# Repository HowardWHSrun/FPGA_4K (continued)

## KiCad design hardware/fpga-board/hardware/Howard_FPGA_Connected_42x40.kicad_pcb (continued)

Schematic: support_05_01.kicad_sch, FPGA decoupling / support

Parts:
C1: 680uF; CP_EIA-7343-43_Kemet-X__C1; Tolerance TBD; Voltage rating TBD; MPN TBD
C2: 4.7uF; C_0402_1005Metric__C2; Tolerance 10%; Voltage rating 10 V; MPN C1005X5R1A475K050BC
C3: 4.7uF; C_0402_1005Metric__C3; Tolerance 10%; Voltage rating 10 V; MPN C1005X5R1A475K050BC
C4: 4.7uF; C_0402_1005Metric__C4; Tolerance 10%; Voltage rating 10 V; MPN C1005X5R1A475K050BC
C5: 4.7uF; C_0402_1005Metric__C5; Tolerance 10%; Voltage rating 10 V; MPN C1005X5R1A475K050BC
C6: 4.7uF; C_0402_1005Metric__C6; Tolerance 10%; Voltage rating 10 V; MPN C1005X5R1A475K050BC
C7: 4.7uF; C_0402_1005Metric__C7; Tolerance 10%; Voltage rating 10 V; MPN C1005X5R1A475K050BC
C8: 4.7uF; C_0402_1005Metric__C8; Tolerance 10%; Voltage rating 10 V; MPN C1005X5R1A475K050BC
C9: 4.7uF; C_0402_1005Metric__C9; Tolerance 10%; Voltage rating 10 V; MPN C1005X5R1A475K050BC
C10: 4.7uF; C_0402_1005Metric__C10; Tolerance 10%; Voltage rating 10 V; MPN C1005X5R1A475K050BC
C11: 4.7uF; C_0402_1005Metric__C11; Tolerance 10%; Voltage rating 10 V; MPN C1005X5R1A475K050BC
C12: 4.7uF; C_0402_1005Metric__C12; Tolerance 10%; Voltage rating 10 V; MPN C1005X5R1A475K050BC
C13: 4.7uF; C_0402_1005Metric__C13; Tolerance 10%; Voltage rating 10 V; MPN C1005X5R1A475K050BC
C14: 0.47uF; C_0201_0603Metric__C14; Tolerance 20%; Voltage rating 10 V; MPN C0603X5R1A474M030BC
C15: 0.47uF; C_0201_0603Metric__C15; Tolerance 20%; Voltage rating 10 V; MPN C0603X5R1A474M030BC
C16: 0.47uF; C_0201_0603Metric__C16; Tolerance 20%; Voltage rating 10 V; MPN C0603X5R1A474M030BC

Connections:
+1V0: C1.1, C2.1, C3.1, C4.1, C5.1, C6.1, C7.1, C8.1, C9.1, C10.1, C11.1, C12.1, C13.1, C14.1, C15.1, C16.1; also elsewhere on the board
GND: C1.2, C2.2, C3.2, C4.2, C5.2, C6.2, C7.2, C8.2, C9.2, C10.2, C11.2, C12.2, C13.2, C14.2, C15.2, C16.2; also elsewhere on the board

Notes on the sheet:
GLOBAL LABELS ARE ELECTRICAL CONNECTIONS. TBD values are unresolved parts. DNP positions are optional or isolation provisions; open pins
FPGA decoupling / support
remain visible to ERC.

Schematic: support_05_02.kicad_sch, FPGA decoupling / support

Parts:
C17: 0.47uF; C_0201_0603Metric__C17; Tolerance 20%; Voltage rating 10 V; MPN C0603X5R1A474M030BC
C18: 0.47uF; C_0201_0603Metric__C18; Tolerance 20%; Voltage rating 10 V; MPN C0603X5R1A474M030BC
C19: 0.47uF; C_0201_0603Metric__C19; Tolerance 20%; Voltage rating 10 V; MPN C0603X5R1A474M030BC
C20: 0.47uF; C_0201_0603Metric__C20; Tolerance 20%; Voltage rating 10 V; MPN C0603X5R1A474M030BC
C21: 0.47uF; C_0201_0603Metric__C21; Tolerance 20%; Voltage rating 10 V; MPN C0603X5R1A474M030BC
C22: 0.47uF; C_0201_0603Metric__C22; Tolerance 20%; Voltage rating 10 V; MPN C0603X5R1A474M030BC
C23: 0.47uF; C_0201_0603Metric__C23; Tolerance 20%; Voltage rating 10 V; MPN C0603X5R1A474M030BC
C24: 0.47uF; C_0201_0603Metric__C24; Tolerance 20%; Voltage rating 10 V; MPN C0603X5R1A474M030BC
C25: 0.47uF; C_0201_0603Metric__C25; Tolerance 20%; Voltage rating 10 V; MPN C0603X5R1A474M030BC
C26: 0.47uF; C_0201_0603Metric__C26; Tolerance 20%; Voltage rating 10 V; MPN C0603X5R1A474M030BC
C27: 0.47uF; C_0201_0603Metric__C27; Tolerance 20%; Voltage rating 10 V; MPN C0603X5R1A474M030BC
C28: 100uF; C_1210_3225Metric__C28; Tolerance TBD; Voltage rating TBD; MPN TBD
C29: 0.47uF; C_0201_0603Metric__C29; Tolerance 20%; Voltage rating 10 V; MPN C0603X5R1A474M030BC
C30: 0.47uF; C_0201_0603Metric__C30; Tolerance 20%; Voltage rating 10 V; MPN C0603X5R1A474M030BC
C31: 0.47uF; C_0201_0603Metric__C31; Tolerance 20%; Voltage rating 10 V; MPN C0603X5R1A474M030BC
C32: 47uF; C_1210_3225Metric__C32; Tolerance TBD; Voltage rating TBD; MPN TBD

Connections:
+1V0: C17.1, C18.1, C19.1, C20.1, C21.1, C22.1, C23.1, C24.1, C25.1, C26.1, C27.1, C28.1, C29.1, C30.1, C31.1; also elsewhere on the board
+1V8: C32.1; also elsewhere on the board
GND: C17.2, C18.2, C19.2, C20.2, C21.2, C22.2, C23.2, C24.2, C25.2, C26.2, C27.2, C28.2, C29.2, C30.2, C31.2, C32.2; also elsewhere on the board

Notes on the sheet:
GLOBAL LABELS ARE ELECTRICAL CONNECTIONS. TBD values are unresolved parts. DNP positions are optional or isolation provisions; open pins
FPGA decoupling / support
remain visible to ERC.

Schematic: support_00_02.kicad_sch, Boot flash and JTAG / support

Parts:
C101: 100nF; C_0402_1005Metric__C101; Tolerance 10%; Voltage rating 16 V; MPN C1005X7R1C104K050BC
C102: 1uF; C_0402_1005Metric__C102; Tolerance 10%; Voltage rating 35 V; MPN C1005X5R1V105K050BC
R115: 0Ohm; R_0201_0603Metric__R115; Tolerance jumper <=50mOhm; Voltage rating 30 V limiting voltage; MPN CRCW02010000Z0ED

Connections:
+3V3: C101.1, C102.1; also elsewhere on the board
GND: C101.2, C102.2; also elsewhere on the board
QSPI_IO3: R115.2; also elsewhere on the board
QSPI_IO3_FPGA: R115.1; also elsewhere on the board

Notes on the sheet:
GLOBAL LABELS ARE ELECTRICAL CONNECTIONS. TBD values are unresolved parts. DNP positions are optional or isolation provisions; open pins
Boot flash and JTAG / support
remain visible to ERC.

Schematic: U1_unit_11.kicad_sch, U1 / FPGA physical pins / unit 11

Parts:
U1: XC7A200T-1SBG484C; Xilinx_SBG484__U1; Tolerance TBD; Voltage rating TBD; MPN XC7A200T-1SBG484C

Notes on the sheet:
U1 / FPGA physical pins / unit 11
bank plan or timing constraints.
Exact XC7A200T SBG484 physical pin map. Boot and core rails are drafted. Unassigned acquisition/link/DDR pins remain open; no completed

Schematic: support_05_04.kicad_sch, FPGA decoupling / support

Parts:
C49: 4.7uF; C_0402_1005Metric__C49; Tolerance 10%; Voltage rating 10 V; MPN C1005X5R1A475K050BC
C50: 4.7uF; C_0402_1005Metric__C50; Tolerance 10%; Voltage rating 10 V; MPN C1005X5R1A475K050BC
C51: 0.47uF; C_0201_0603Metric__C51; Tolerance 20%; Voltage rating 10 V; MPN C0603X5R1A474M030BC
C52: 0.47uF; C_0201_0603Metric__C52; Tolerance 20%; Voltage rating 10 V; MPN C0603X5R1A474M030BC
C53: 0.47uF; C_0201_0603Metric__C53; Tolerance 20%; Voltage rating 10 V; MPN C0603X5R1A474M030BC
C54: 0.47uF; C_0201_0603Metric__C54; Tolerance 20%; Voltage rating 10 V; MPN C0603X5R1A474M030BC
C55: 47uF; C_1210_3225Metric__C55; Tolerance TBD; Voltage rating TBD; MPN TBD
C56: 4.7uF; C_0402_1005Metric__C56; Tolerance 10%; Voltage rating 10 V; MPN C1005X5R1A475K050BC
C57: 4.7uF; C_0402_1005Metric__C57; Tolerance 10%; Voltage rating 10 V; MPN C1005X5R1A475K050BC
C58: 0.47uF; C_0201_0603Metric__C58; Tolerance 20%; Voltage rating 10 V; MPN C0603X5R1A474M030BC
C59: 0.47uF; C_0201_0603Metric__C59; Tolerance 20%; Voltage rating 10 V; MPN C0603X5R1A474M030BC
C60: 0.47uF; C_0201_0603Metric__C60; Tolerance 20%; Voltage rating 10 V; MPN C0603X5R1A474M030BC
C61: 0.47uF; C_0201_0603Metric__C61; Tolerance 20%; Voltage rating 10 V; MPN C0603X5R1A474M030BC
C62: 47uF; C_1210_3225Metric__C62; Tolerance TBD; Voltage rating TBD; MPN TBD
C63: 4.7uF; C_0402_1005Metric__C63; Tolerance 10%; Voltage rating 10 V; MPN C1005X5R1A475K050BC
C64: 4.7uF; C_0402_1005Metric__C64; Tolerance 10%; Voltage rating 10 V; MPN C1005X5R1A475K050BC

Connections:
+3V3: C49.1, C50.1, C51.1, C52.1, C53.1, C54.1, C55.1; also elsewhere on the board
GND: C49.2, C50.2, C51.2, C52.2, C53.2, C54.2, C55.2, C56.2, C57.2, C58.2, C59.2, C60.2, C61.2, C62.2, C63.2, C64.2; also elsewhere on the board
VCCO_15_TBD: C56.1, C57.1, C58.1, C59.1, C60.1, C61.1, C62.1; also elsewhere on the board
VCCO_16_TBD: C63.1, C64.1; also elsewhere on the board

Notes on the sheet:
GLOBAL LABELS ARE ELECTRICAL CONNECTIONS. TBD values are unresolved parts. DNP positions are optional or isolation provisions; open pins
FPGA decoupling / support
remain visible to ERC.

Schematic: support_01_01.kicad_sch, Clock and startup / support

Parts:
C120: TBD oscillator bypass; C_0603_1608Metric__C120; Tolerance TBD; Voltage rating TBD; MPN TBD
R120: TBD clock series resistor; R_0402_1005Metric__R120; Tolerance TBD; Voltage rating TBD; MPN TBD
R121: TBD oscillator control resistor; R_0402_1005Metric__R121; Tolerance TBD; Voltage rating TBD; MPN TBD
Y1: Oscillator frequency / MPN TBD; Oscillator_SMD_Abracon_ASE-4Pin_3.2x2.5mm__Y1; Tolerance TBD; Voltage rating TBD; MPN TBD

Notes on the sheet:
GLOBAL LABELS ARE ELECTRICAL CONNECTIONS. TBD values are unresolved parts. DNP positions are optional or isolation provisions; open pins
remain visible to ERC.
Clock and startup / support

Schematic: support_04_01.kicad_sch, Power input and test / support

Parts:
F1: FUSE / rating TBD; Fuse_1206_3216Metric__F1; Tolerance TBD; Voltage rating TBD; MPN TBD
J5: DC INPUT / 12V proposal; JST_PH_B2B-PH-K_1x02_P2.00mm_Vertical__J5; Tolerance TBD; Voltage rating TBD; MPN TBD
TP1: GND; TestPoint_Pad_D1.0mm__TP1; Tolerance TBD; Voltage rating TBD; MPN PCB copper test pad
TP2: VIN_PROTECTED; TestPoint_Pad_D1.0mm__TP2; Tolerance TBD; Voltage rating TBD; MPN PCB copper test pad
TP3: +1V0; TestPoint_Pad_D1.0mm__TP3; Tolerance TBD; Voltage rating TBD; MPN PCB copper test pad
TP4: +1V8; TestPoint_Pad_D1.0mm__TP4; Tolerance TBD; Voltage rating TBD; MPN PCB copper test pad
TP5: +1V5; TestPoint_Pad_D1.0mm__TP5; Tolerance TBD; Voltage rating TBD; MPN PCB copper test pad
TP6: +3V3; TestPoint_Pad_D1.0mm__TP6; Tolerance TBD; Voltage rating TBD; MPN PCB copper test pad
TP7: PROGRAM_B; TestPoint_Pad_D1.0mm__TP7; Tolerance TBD; Voltage rating TBD; MPN PCB copper test pad
TP8: DONE; TestPoint_Pad_D1.0mm__TP8; Tolerance TBD; Voltage rating TBD; MPN PCB copper test pad

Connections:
+1V0: TP3.1; also elsewhere on the board
+1V5: TP5.1; also elsewhere on the board
+1V8: TP4.1; also elsewhere on the board
+3V3: TP6.1; also elsewhere on the board
DONE: TP8.1; also elsewhere on the board
GND: J5.2, TP1.1; also elsewhere on the board
PROGRAM_B: TP7.1; also elsewhere on the board
VIN_PROTECTED: F1.2, TP2.1; also elsewhere on the board
VIN_RAW: F1.1, J5.1

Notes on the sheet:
GLOBAL LABELS ARE ELECTRICAL CONNECTIONS. TBD values are unresolved parts. DNP positions are optional or isolation provisions; open pins
Power input and test / support
remain visible to ERC.

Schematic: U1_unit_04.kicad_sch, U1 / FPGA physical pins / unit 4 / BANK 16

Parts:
U1: XC7A200T-1SBG484C; Xilinx_SBG484__U1; Tolerance TBD; Voltage rating TBD; MPN XC7A200T-1SBG484C

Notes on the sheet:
U1 / FPGA physical pins / unit 4 / BANK 16
bank plan or timing constraints.
Exact XC7A200T SBG484 physical pin map. Boot and core rails are drafted. Unassigned acquisition/link/DDR pins remain open; no completed

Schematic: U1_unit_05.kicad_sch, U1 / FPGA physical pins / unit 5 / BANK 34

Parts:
U1: XC7A200T-1SBG484C; Xilinx_SBG484__U1; Tolerance TBD; Voltage rating TBD; MPN XC7A200T-1SBG484C

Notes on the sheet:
bank plan or timing constraints.
Exact XC7A200T SBG484 physical pin map. Boot and core rails are drafted. Unassigned acquisition/link/DDR pins remain open; no completed
U1 / FPGA physical pins / unit 5 / BANK 34

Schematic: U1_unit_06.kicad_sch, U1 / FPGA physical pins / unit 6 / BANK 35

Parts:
U1: XC7A200T-1SBG484C; Xilinx_SBG484__U1; Tolerance TBD; Voltage rating TBD; MPN XC7A200T-1SBG484C

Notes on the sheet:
bank plan or timing constraints.
U1 / FPGA physical pins / unit 6 / BANK 35
Exact XC7A200T SBG484 physical pin map. Boot and core rails are drafted. Unassigned acquisition/link/DDR pins remain open; no completed

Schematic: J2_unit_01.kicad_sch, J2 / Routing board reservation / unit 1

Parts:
J2: Routing 80-contact / proxy; Hirose_DF40C-80DS-0.4V_2x40_P0.4mm__J2; Tolerance TBD; Voltage rating TBD; MPN TBD

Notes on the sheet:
and Gerald.
J2 / Routing board reservation / unit 1
Routing-to-FPGA connector SPACE RESERVATION B. Coordinate carrier revision, grounds, clock/control sharing and power handoff with Zitong

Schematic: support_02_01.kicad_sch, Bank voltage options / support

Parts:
R130: 0R / DNP; R_0402_1005Metric__R130; Tolerance TBD; Voltage rating TBD; MPN TBD; not fitted
R131: 0R / DNP; R_0402_1005Metric__R131; Tolerance TBD; Voltage rating TBD; MPN TBD; not fitted
R132: 0R / DNP; R_0402_1005Metric__R132; Tolerance TBD; Voltage rating TBD; MPN TBD; not fitted
R133: 0R / DNP; R_0402_1005Metric__R133; Tolerance TBD; Voltage rating TBD; MPN TBD; not fitted
R134: 0R / DNP; R_0402_1005Metric__R134; Tolerance TBD; Voltage rating TBD; MPN TBD; not fitted

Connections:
+1V5: R131.1, R132.1, R133.1, R134.1; also elsewhere on the board
+3V3: R130.1; also elsewhere on the board
VCCO_13_TBD: R130.2; also elsewhere on the board
VCCO_15_TBD: R131.2; also elsewhere on the board
VCCO_16_TBD: R132.2; also elsewhere on the board
VCCO_34_TBD: R133.2; also elsewhere on the board
VCCO_35_TBD: R134.2; also elsewhere on the board

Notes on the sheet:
GLOBAL LABELS ARE ELECTRICAL CONNECTIONS. TBD values are unresolved parts. DNP positions are optional or isolation provisions; open pins
Bank voltage options / support
remain visible to ERC.

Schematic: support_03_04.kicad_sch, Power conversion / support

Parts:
C319: 100uF 6.3V local-output PROVISIONAL; C_1210_3225Metric__C319; Tolerance TBD; Voltage rating TBD; MPN TBD
C320: 100uF 6.3V local-output PROVISIONAL; C_1210_3225Metric__C320; Tolerance TBD; Voltage rating TBD; MPN TBD
C321: 47uF 6.3V local-output PROVISIONAL; C_1210_3225Metric__C321; Tolerance TBD; Voltage rating TBD; MPN TBD
C322: 47uF 6.3V local-output PROVISIONAL; C_1210_3225Metric__C322; Tolerance TBD; Voltage rating TBD; MPN TBD
C323: 47uF 6.3V local-output PROVISIONAL; C_1210_3225Metric__C323; Tolerance TBD; Voltage rating TBD; MPN TBD
C324: 22uF 6.3V local-output PROVISIONAL; C_1210_3225Metric__C324; Tolerance TBD; Voltage rating TBD; MPN TBD
C325: 22uF 6.3V local-output PROVISIONAL; C_1210_3225Metric__C325; Tolerance TBD; Voltage rating TBD; MPN TBD
C326: 22uF 6.3V local-output PROVISIONAL; C_1210_3225Metric__C326; Tolerance TBD; Voltage rating TBD; MPN TBD
C327: 22uF 6.3V local-output PROVISIONAL; C_1210_3225Metric__C327; Tolerance TBD; Voltage rating TBD; MPN TBD

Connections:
+1V0: C319.1, C320.1; also elsewhere on the board
+1V5: C324.1, C325.1; also elsewhere on the board
+1V8: C321.1, C322.1, C323.1; also elsewhere on the board
+3V3: C326.1, C327.1; also elsewhere on the board
GND: C319.2, C320.2, C321.2, C322.2, C323.2, C324.2, C325.2, C326.2, C327.2; also elsewhere on the board

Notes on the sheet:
GLOBAL LABELS ARE ELECTRICAL CONNECTIONS. TBD values are unresolved parts. DNP positions are optional or isolation provisions; open pins
Power conversion / support
remain visible to ERC.

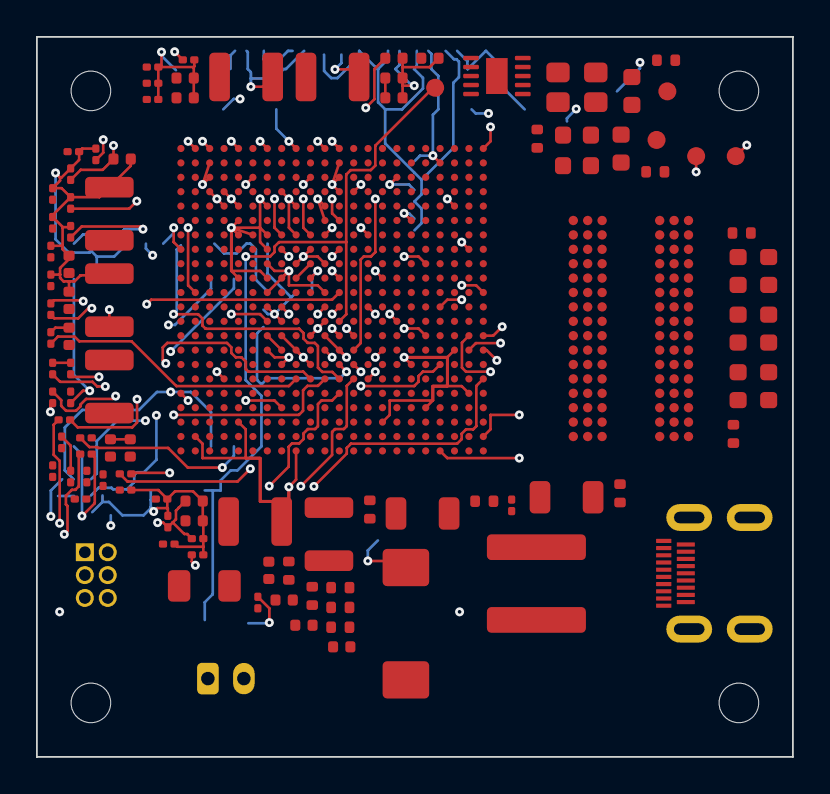
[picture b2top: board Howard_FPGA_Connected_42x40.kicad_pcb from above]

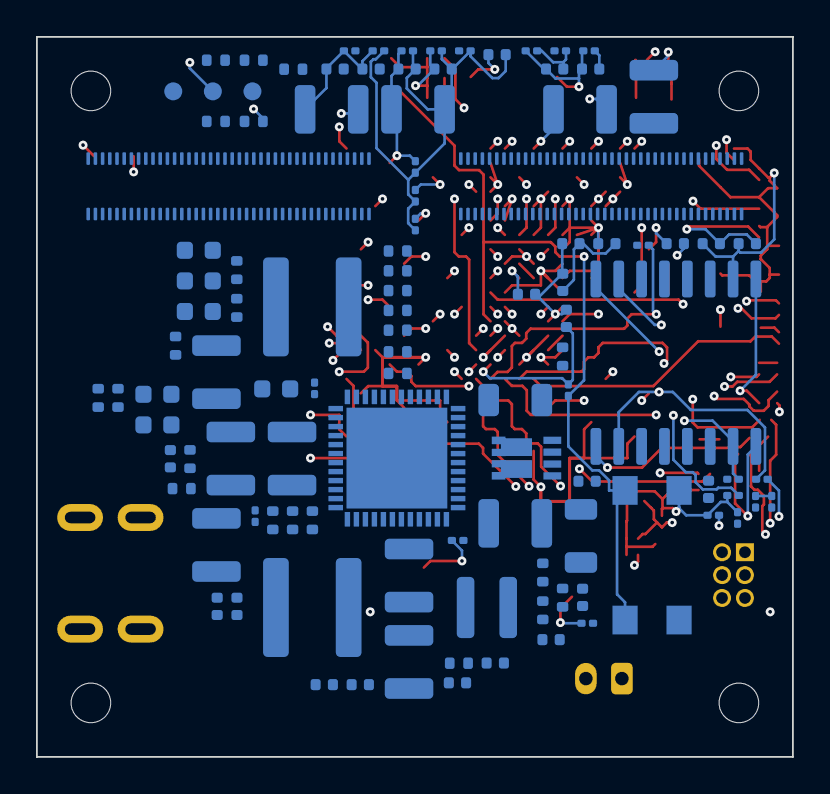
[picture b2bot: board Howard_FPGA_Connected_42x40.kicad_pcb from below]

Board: 8 copper layers, 42.0 x 40.0 mm, 214 parts (108 on the bottom side), 65 nets.

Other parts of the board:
J3: Micro-HDMI / custom-link pinout TBD; HDMI_Micro-D_Molex_46765-1xxx__J3

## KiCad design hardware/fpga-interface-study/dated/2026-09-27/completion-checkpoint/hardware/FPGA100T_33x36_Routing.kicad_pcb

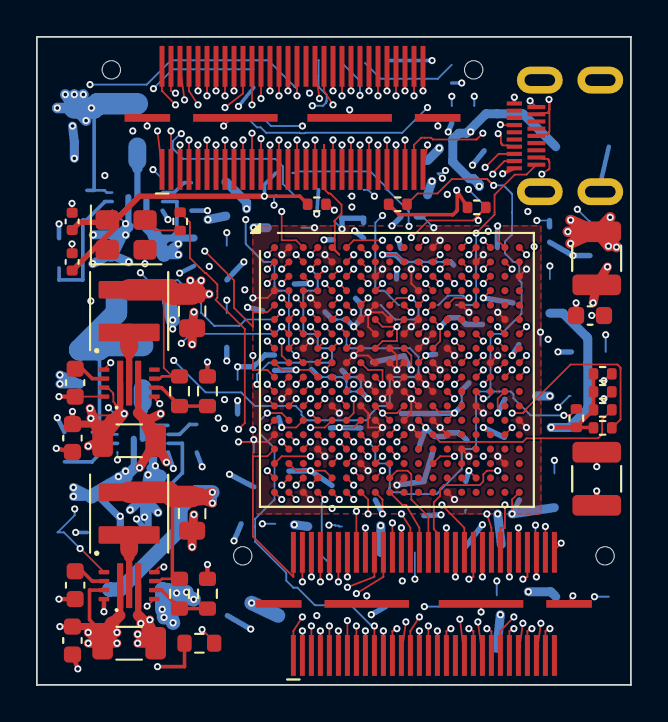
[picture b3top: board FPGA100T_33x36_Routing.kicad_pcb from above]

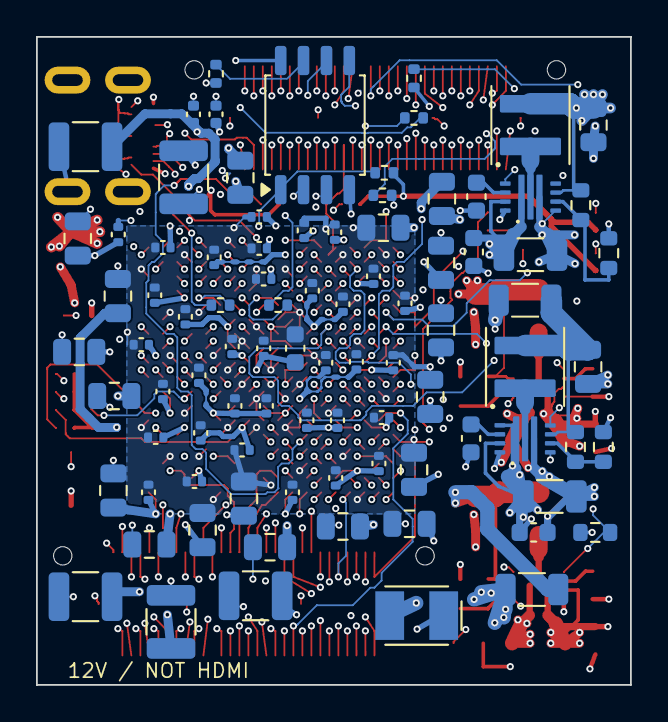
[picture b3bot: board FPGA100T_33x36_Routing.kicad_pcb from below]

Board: 12 copper layers, 33.0 x 36.0 mm, 125 parts (89 on the bottom side), 159 nets.

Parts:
C1: 47u 25V X5R; Capacitor_SMD__C_1210_3225Metric
C2, C4, C8, C12, C16: 100n 100V X7R; Capacitor_SMD__C_0603_1608Metric
C3, C7, C11, C15: 22u 25V X5R; Capacitor_SMD__C_1206_3216Metric
C5, C9, C13, C17: 22u 16V X5R; Capacitor_SMD__C_0805_2012Metric
C6, C10, C14, C18: 10n 50V X7R; Capacitor_SMD__C_0603_1608Metric
C20: 330u 2.5V POSCAP ESR9m@300kHz; Panasonic_POSCAP_B2_Recommended
C21: 100u 6.3V X5R; Capacitor_SMD__C_1210_3225Metric
C22, C23, C24, C25, C26, C27, C41, C42, C51, C52, C57, C58, C64, C65, C70, C71, C76, C77: 4.7u 10V X7R; Capacitor_SMD__C_0805_2012Metric
C28, C29, C30, C31, C32, C33, C34, C35, C36, C37, C43, C44, C45, C46, C53, C54, C55, C56, C59, C60, C61, C62, C66, C67, C68, C69, C72, C73, C74, C75, C78, C79, C80, C81: 470n 10V X7R; Murata_GRT15_0402_Recommended
C40, C50, C63, C82, C92: 47u 6.3V X7R; Capacitor_SMD__C_1210_3225Metric
C90: 100n 16V X7R; Murata_GRT15_0402_Recommended
C91: 1u 10V X7R; Capacitor_SMD__C_0603_1608Metric
C100, C103: 100n; Capacitor_SMD__C_0402_1005Metric
C101: 1u 16V X5R; Capacitor_SMD__C_0402_1005Metric
C102: 10n; Capacitor_SMD__C_0402_1005Metric
J4: CUSTOM POWER + JTAG / DATA TBD; LinkPort__MicroHDMI_46765_1xxx
J5, J6: QSH-030-01-L-D-A; Samtec_QSH-030-01-L-D-A
L1, L2, L3, L4: 1uH 5.4A Isat30%; PowerDraft__L_Coilcraft_XFL4020
R1: 32.4k 0.1%; Resistor_SMD__R_0603_1608Metric
R2, R4, R6, R8: 69.8k 0.1%; Resistor_SMD__R_0603_1608Metric
R3: 110k 0.1%; Resistor_SMD__R_0603_1608Metric
R5: 180k 0.1%; Resistor_SMD__R_0603_1608Metric
R7: 80.6k 0.1%; Resistor_SMD__R_0603_1608Metric
R9: 12m 1% 1W; Resistor_SMD__R_1206_3216Metric
R10, R11: 100k; Resistor_SMD__R_0603_1608Metric
R100: 2.4k; Resistor_SMD__R_0402_1005Metric
R101, R102, R108, R109, R110: 4.7k; Resistor_SMD__R_0402_1005Metric
R103, R105, R118, R119: 33; Resistor_SMD__R_0402_1005Metric
R104: 0; Resistor_SMD__R_0402_1005Metric
R111, R114: 1k; Resistor_SMD__R_0402_1005Metric
R115, R116, R117: 10k; Resistor_SMD__R_0402_1005Metric
R122: 15m 1% 1W; Resistor_SMD__R_1206_3216Metric
U1: XC7A100T-1CSG324I; Xilinx_CSG324
U2, U3, U4, U5: TPS62135RGXR; PowerDraft__Texas_VQFN_RGX0011A_2x3mm
U6: MX25U12835FM2I-10G; Package_SO__SOIC-8_5_3x5_3mm_P1_27mm
Y1: ASE3 32MHz 1.8V; Oscillator__Oscillator_SMD_Abracon_ASE-4Pin_3_2x2_5mm

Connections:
ASIC1_CLK32MHz_Out: J5.9, U1.E2
ASIC1_DATA1: J5.1, U1.K1
ASIC1_DATA2: J5.2, U1.F1
ASIC1_DATA3: J5.3, U1.K2
ASIC1_DATA4: J5.4, U1.E1
ASIC1_DATA5: J5.5, U1.H1
ASIC1_DATA6: J5.6, U1.G2
ASIC1_DATA7: J5.7, U1.G1
ASIC1_DATA8: J5.8, U1.C1
ASIC1_READ: J5.10, U1.B1
ASIC1_SYNC: J5.11, U1.J2
ASIC2_CLK32MHz_Out: J5.20, U1.E3
ASIC2_DATA1: J5.12, U1.C2
ASIC2_DATA2: J5.13, U1.H2
ASIC2_DATA3: J5.14, U1.B3
ASIC2_DATA4: J5.15, U1.J3
ASIC2_DATA5: J5.16, U1.A3
ASIC2_DATA6: J5.17, U1.G3
ASIC2_DATA7: J5.18, U1.C4
ASIC2_DATA8: J5.19, U1.A1
ASIC2_READ: J5.21, U1.B2
ASIC2_SYNC: J5.22, U1.B4
ASIC3_CLK32MHz_Out: J5.31, U1.F4
ASIC3_DATA1: J5.23, U1.J4
ASIC3_DATA2: J5.24, U1.J5
ASIC3_DATA3: J5.25, U1.H4
ASIC3_DATA4: J5.26, U1.F5
ASIC3_DATA5: J5.27, U1.G4
ASIC3_DATA6: J5.28, U1.E5
ASIC3_DATA7: J5.29, U1.H5
ASIC3_DATA8: J5.30, U1.G6
ASIC3_READ: J5.32, U1.E6
ASIC3_SYNC: J5.33, U1.H6
ASIC4_CLK32MHz_Out: J5.42, U1.D5
ASIC4_DATA1: J6.60, U1.C5
ASIC4_DATA2: J5.35, U1.A4
ASIC4_DATA3: J5.36, U1.C6
ASIC4_DATA4: J5.37, U1.A5
ASIC4_DATA5: J5.38, U1.A6
ASIC4_DATA6: J5.39, U1.B6
ASIC4_DATA7: J5.40, U1.C7
ASIC4_DATA8: J5.41, U1.E7
ASIC4_READ: J5.43, U1.B7
ASIC4_SYNC: J5.44, U1.D8
ASIC5_CLK32MHz_Out: J6.9, U1.R3
ASIC5_DATA1: J6.1, U1.V1
ASIC5_DATA2: J6.2, U1.R1
ASIC5_DATA3: J6.3, U1.U1
ASIC5_DATA4: J6.4, U1.U2
ASIC5_DATA5: J6.5, U1.T1
ASIC5_DATA6: J6.6, U1.R2
ASIC5_DATA7: J6.7, U1.V2
ASIC5_DATA8: J6.8, U1.U3
ASIC5_READ: J6.10, U1.V4
ASIC5_SYNC: J6.11, U1.P2
ASIC6_CLK32MHz_Out: J6.20, U1.P4
ASIC6_DATA1: J6.12, U1.M2
ASIC6_DATA2: J6.13, U1.N1
ASIC6_DATA3: J6.14, U1.M3
ASIC6_DATA4: J6.15, U1.M1
ASIC6_DATA5: J6.16, U1.K3
ASIC6_DATA6: J6.17, U1.L1
ASIC6_DATA7: J6.18, U1.N4
ASIC6_DATA8: J6.19, U1.N2
ASIC6_READ: J6.21, U1.L3
ASIC6_SYNC: J6.22, U1.R6
ASIC7_CLK32MHz_Out: J6.31, U1.T5
ASIC7_DATA1: J6.23, U1.U4
ASIC7_DATA2: J6.24, U1.V7
ASIC7_DATA3: J6.25, U1.V5
ASIC7_DATA4: J6.26, U1.U7
ASIC7_DATA5: J6.27, U1.V6
ASIC7_DATA6: J6.28, U1.U8
ASIC7_DATA7: J6.29, U1.U6
ASIC7_DATA8: J6.30, U1.V9
ASIC7_READ: J6.32, U1.U9
ASIC7_SYNC: J6.33, U1.T6
ASIC8_CLK32MHz_Out: J6.42, U1.N5
ASIC8_DATA1: J6.34, U1.M6
ASIC8_DATA2: J6.35, U1.M4
ASIC8_DATA3: J6.36, U1.R8
ASIC8_DATA4: J6.58, U1.L4
ASIC8_DATA5: J6.38, U1.K5
ASIC8_DATA6: J6.39, U1.R7
ASIC8_DATA7: J6.40, U1.L6
ASIC8_DATA8: J6.41, U1.N6
ASIC8_READ: J6.43, U1.T8
ASIC8_SYNC: J6.44, U1.K6
BOARD1_CLK: J5.54, U1.B16
BOARD1_SPI_CLK: J5.58, U1.B17
BOARD2_CLK: J5.55, U1.B13
BOARD2_SPI_CLK: J5.59, U1.A14
BOARD3_CLK: J5.56, U1.A16
BOARD3_SPI_CLK: J5.60, U1.A18
BOARD4_CLK: J5.57, U1.C14
BOARD4_SPI_CLK: J6.45, U1.K13
CFG_M0: R111.2, U1.P12
CFG_PUDC_B: R114.2, U1.L15
CHIP_RESET_SHARED: J5.45, U1.D12
CLK_32MHZ: R119.2, U1.P17
FB_ASIC: R7.2, R8.1, U5.5
FB_AUX: R3.2, R4.1, U3.5
FB_CFG: R5.2, R6.1, U4.5
FB_CORE: R1.2, R2.1, U2.5
FE_RESET_SHARED: J5.48, U1.B14
FLASH_CS_B: R100.2, U1.L13, U6.1
FLASH_DQ0: R104.2, U6.5
FLASH_DQ1: R105.2, U6.2
FLASH_DQ2: R101.2, U6.3
FLASH_DQ3: R102.2, U6.7
FLASH_SCLK: R103.2, U6.6
FPGA_CCLK: R103.1, U1.E9
FPGA_CFG_DQ0: R104.1, U1.K17
FPGA_CFG_DQ1: R105.1, U1.K18
FPGA_DONE: R110.2, U1.P10
FPGA_INIT_B: R109.2, U1.P7
FPGA_PROGRAM_B: R108.2, U1.P9
FPGA_TDO: R118.1, U1.E13
GND: C1.2, C2.2, C3.2, C4.2, C5.2, C6.2, C7.2, C8.2, C9.2, C10.2, C11.2, C12.2, C13.2, C14.2, C15.2, C16.2, C17.2, C18.2, C20.2, C21.2, C22.2, C23.2, C24.2, C25.2, C26.2, C27.2, C28.2, C29.2, C30.2, C31.2, C32.2, C33.2, C34.2, C35.2, C36.2, C37.2, C40.2, C41.2, C42.2, C43.2, C44.2, C45.2, C46.2, C50.2, C51.2, C52.2, C53.2, C54.2, C55.2, C56.2, C57.2, C58.2, C59.2, C60.2, C61.2, C62.2, C63.2, C64.2, C65.2, C66.2, C67.2, C68.2, C69.2, C70.2, C71.2, C72.2, C73.2, C74.2, C75.2, C76.2, C77.2, C78.2, C79.2, C80.2, C81.2, C82.2, C90.2, C91.2, C92.2, C100.2, C101.2, C102.2, C103.2, J4.4, J4.7, J4.10, J4.13, J4.16, J4.SH, J5.G, J6.G, R2.2, R4.2, R6.2, R8.2, U1.A2, U1.A12, U1.B5, U1.B15, U1.C8, U1.C18, U1.D1, U1.D11, U1.E4, U1.E8, U1.E14, U1.F7, U1.F9, U1.F11, U1.F17, U1.G8, U1.G10, U1.G12, U1.H3, U1.H7, U1.H9, U1.H11, U1.H13, U1.J6, U1.J8, U1.J9, U1.J10, U1.J12, U1.J16, U1.K7, U1.K9, U1.K10, U1.K11, U1.L2, U1.L8, U1.L9, U1.L10, U1.L12, U1.M5, U1.M7, U1.M9, U1.M11, U1.M15, U1.N8, U1.N10, U1.N12, U1.N18, U1.P1, U1.P8, U1.P11, U1.P13, U1.R4, U1.R14, U1.T7, U1.T17, U1.U10, U1.V3, U1.V13, U2.3, U2.4, U2.11, U3.3, U3.4, U3.11, U4.3, U4.4, U4.11, U5.3, U5.4, U5.11, U6.4, Y1.2
IMP_TST_SHARED: J5.47, U1.B11
JTAG_TCK: J4.17, R117.2, U1.E10
JTAG_TDI: J4.15, R116.2, U1.E11
JTAG_TDO: J4.18, R118.2
JTAG_TMS: J4.2, R115.2, U1.E12
LINK_12V: C1.1, C2.1, C3.1, C4.1, C7.1, C8.1, C11.1, C12.1, C15.1, C16.1, J4.19, R10.1, R11.1, U2.1, U2.8, U2.10, U3.1, U3.10, U4.1, U4.10, U5.1, U5.10
NONSTIM_BOARD1_SPI_DL: J6.54, U1.G17
NONSTIM_BOARD1_SPI_DR: J6.55, U1.H17
NONSTIM_BOARD2_SPI_DL: J6.56, U1.J18
NONSTIM_BOARD2_SPI_DR: J6.57, U1.G18
OSC_32M_RAW: R119.1, Y1.3
PG_AUX: R11.2, U3.7, U4.8, U5.8
PG_CORE: R10.2, U2.7, U3.8
SPI_LATCH_SHARED: J5.49, U1.A11
SS_ASIC: C18.1, U5.9
SS_AUX: C10.1, U3.9
SS_CFG: C14.1, U4.9
SS_CORE: C6.1, U2.9
STIM_CHB_SHARED: J5.53, U1.B12
STIM_CHIP1_SPI_DL: J6.46, U1.J14
STIM_CHIP1_SPI_DR: J6.47, U1.J13
STIM_CHIP2_SPI_DL: J6.48, U1.G14
STIM_CHIP2_SPI_DR: J6.49, U1.H14
STIM_CHIP3_SPI_DL: J6.50, U1.J15
STIM_CHIP3_SPI_DR: J6.51, U1.K15
STIM_CHIP4_SPI_DL: J6.52, U1.J17
STIM_CHIP4_SPI_DR: J6.53, U1.K16
STIM_CLK_SHARED: J5.50, U1.C16
STIM_EN_SHARED: J5.52, U1.A15
STIM_START_SHARED: J5.51, U1.C12
SW_ASIC: L4.1, U5.2
SW_AUX: L2.1, U3.2
SW_CFG: L3.1, U4.2
SW_CORE: L1.1, U2.2
VAUX_REG_1V803: C9.1, L2.2, R3.1, R122.1, U3.6
VCCAUX_1V8: C40.1, C41.1, C42.1, C43.1, C44.1, C45.1, C46.1, C50.1, C51.1, C52.1, C53.1, C54.1, C55.1, C56.1, C90.1, C91.1, C92.1, C100.1, C101.1, C102.1, C103.1, J4.1, R100.1, R101.1, R102.1, R108.1, R109.1, R110.1, R111.1, R114.1, R115.1, R116.1, R117.1, R122.2, U1.F12, U1.H10, U1.H12, U1.K12, U1.L17, U1.M12, U1.N13, U1.P16, U1.R9, U1.T12, U1.U15, U1.V18, U6.8, Y1.1, Y1.4
VCCINT_1V0: C20.1, C21.1, C22.1, C23.1, C24.1, C25.1, C26.1, C27.1, C28.1, C29.1, C30.1, C31.1, C32.1, C33.1, C34.1, C35.1, C36.1, C37.1, R9.2, U1.F8, U1.F10, U1.G7, U1.G9, U1.G11, U1.H8, U1.J7, U1.J11, U1.K8, U1.L7, U1.L11, U1.M8, U1.M10, U1.N7, U1.N9, U1.N11
VCC_ASIC_1V5: C17.1, C64.1, C65.1, C66.1, C67.1, C68.1, C69.1, C70.1, C71.1, C72.1, C73.1, C74.1, C75.1, C76.1, C77.1, C78.1, C79.1, C80.1, C81.1, C82.1, L4.2, R7.1, U1.A7, U1.A17, U1.C3, U1.C13, U1.D6, U1.D16, U1.F2, U1.G5, U1.G15, U1.H18, U1.J1, U1.K4, U1.K14, U1.N3, U1.P6, U1.T2, U1.U5, U1.V8, U5.6
VCC_LINK_2V5: C13.1, C57.1, C58.1, C59.1, C60.1, C61.1, C62.1, C63.1, L3.2, R5.1, U1.B10, U4.6
VCORE_REG_1V025: C5.1, L1.2, R1.1, R9.1, U2.6

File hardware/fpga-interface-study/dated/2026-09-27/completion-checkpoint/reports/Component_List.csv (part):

reference,value,group,side,x_mm,y_mm,rotation_deg,footprint,mpn,role_and_limits,datasheet
C1,47u 25V X5R,power_input,Front,31.1,12.3,-90.0,CoreSupport:Capacitor_SMD__C_1210_3225Metric,MSAST32MAB5476MPNDT1,"12V candidate: manufacturer confirms 47uF +/-20%, 25V X5R, 1210, -55 to +85C, preferred part; effective capacitance at 12V, aging, temperature, inrush and power-entry transient performance remain unqualified. Replaces incompatible 10V input capacitor.",https://ds.yuden.co.jp/TYCOMPAS/or/detail?pn=MSAST32MAB5476M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
C2,100n 100V X7R,power_input,Front,30.73,15.48,0.0,CoreSupport:Capacitor_SMD__C_0603_1608Metric,GRM188R72A104KA35D,"12V candidate: manufacturer confirms 100nF +/-10%, 100V X7R, 0603, -55 to +125C and D packing suffix. Input bypass only; this voltage rating does not protect the 17V-rated converter input from cable transients.",https://www.murata.com/products/productdetail?partno=GRM188R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
C3,22u 25V X5R,power_core,Back,4.505,25.529999,180.0,CoreSupport:Capacitor_SMD__C_1206_3216Metric,MSAST31LBB5226MTNA01,12 V design: 22 uF 25 V X5R 1206 correction. Manufacturer typical bias curve gives 6.62332 uF at 12.6 V; 0.8 tolerance and 0.85 temperature screening factors give 4.5038576 uF before aging. Local placement checked; routing integration pending in this separate revision. Typical curves are not guaranteed production minima.,https://ds.yuden.co.jp/TYCOMPAS/or/detail?pn=MSAST31LBB5226M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
C4,100n 100V X7R,power_core,Back,5.405,27.529999,180.0,CoreSupport:Capacitor_SMD__C_0603_1608Metric,GRM188R72A104KA35D,"12V candidate: manufacturer confirms 100nF +/-10%, 100V X7R, 0603, -55 to +125C and D packing suffix. Input bypass only; this voltage rating does not protect the 17V-rated converter input from cable transients.",https://www.murata.com/products/productdetail?partno=GRM188R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
C5,22u 16V X5R,power_core,Back,2.38,18.329999,-90.0,CoreSupport:Capacitor_SMD__C_0805_2012Metric,EMK212BBJ226MG-T,"Engineering draft; verify ordered part and layout before fabrication Independent review: X5R, rated -55 to +85 C; manufacturer renamed alias MSASE21GBB5226MTNA01; effective capacitance and sourcing not qualified.",https://ds-origin.yuden.co.jp/TYCOMPAS/eu/detail?pn=MSASE21G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
C6,10n 50V X7R,power_core,Back,8.88,22.304999,-90.0,CoreSupport:Capacitor_SMD__C_0603_1608Metric,GRM188R71H103KA01D,Engineering draft; verify ordered part and layout before fabrication,https://www.murata.com/en-global/products/productdetail?part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
C7,22u 25V X5R,power_aux,Front,5.125,33.684999,0.0,CoreSupport:Capacitor_SMD__C_1206_3216Metric,MSAST31LBB5226MTNA01,12 V design: 22 uF 25 V X5R 1206 correction. Manufacturer typical bias curve gives 6.62332 uF at 12.6 V; 0.8 tolerance and 0.85 temperature screening factors give 4.5038576 uF before aging. Local placement checked; routing integration pending in this separate revision. Typical curves are not guaranteed production minima.,https://ds.yuden.co.jp/TYCOMPAS/or/detail?pn=MSAST31LBB5226M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
C8,100n 100V X7R,power_aux,Front,1.975,33.534999,-90.0,CoreSupport:Capacitor_SMD__C_0603_1608Metric,GRM188R72A104KA35D,"12V candidate: manufacturer confirms 100nF +/-10%, 100V X7R, 0603, -55 to +125C and D packing suffix. Input bypass only; this voltage rating does not protect the 17V-rated converter input from cable transients.",https://www.murata.com/products/productdetail?partno=GRM188R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
C9,22u 16V X5R,power_aux,Front,8.625,26.485,-90.0,CoreSupport:Capacitor_SMD__C_0805_2012Metric,EMK212BBJ226MG-T,"Engineering draft; verify ordered part and layout before fabrication Independent review: X5R, rated -55 to +85 C; manufacturer renamed alias MSASE21GBB5226MTNA01; effective capacitance and sourcing not qualified.",https://ds-origin.yuden.co.jp/TYCOMPAS/eu/detail?pn=MSASE21G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
C10,10n 50V X7R,power_aux,Front,2.125,30.46,-90.0,CoreSupport:Capacitor_SMD__C_0603_1608Metric,GRM188R71H103KA01D,Engineering draft; verify ordered part and layout before fabrication,https://www.murata.com/en-global/products/productdetail?part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
C11,22u 25V X5R,power_cfg,Front,5.125,22.435,0.0,CoreSupport:Capacitor_SMD__C_1206_3216Metric,MSAST31LBB5226MTNA01,12 V design: 22 uF 25 V X5R 1206 correction. Manufacturer typical bias curve gives 6.62332 uF at 12.6 V; 0.8 tolerance and 0.85 temperature screening factors give 4.5038576 uF before aging. Local placement checked; routing integration pending in this separate revision. Typical curves are not guaranteed production minima.,https://ds.yuden.co.jp/TYCOMPAS/or/detail?pn=MSAST31LBB5226M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
C12,100n 100V X7R,power_cfg,Front,1.975,22.285,-90.0,CoreSupport:Capacitor_SMD__C_0603_1608Metric,GRM188R72A104KA35D,"12V candidate: manufacturer confirms 100nF +/-10%, 100V X7R, 0603, -55 to +125C and D packing suffix. Input bypass only; this voltage rating does not protect the 17V-rated converter input from cable transients.",https://www.murata.com/products/productdetail?partno=GRM188R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
C13,22u 16V X5R,power_cfg,Front,8.625,15.235,-90.0,CoreSupport:Capacitor_SMD__C_0805_2012Metric,EMK212BBJ226MG-T,"Engineering draft; verify ordered part and layout before fabrication Independent review: X5R, rated -55 to +85 C; manufacturer renamed alias MSASE21GBB5226MTNA01; effective capacitance and sourcing not qualified.",https://ds-origin.yuden.co.jp/TYCOMPAS/eu/detail?pn=MSASE21G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
C14,10n 50V X7R,power_cfg,Front,2.125,19.21,-90.0,CoreSupport:Capacitor_SMD__C_0603_1608Metric,GRM188R71H103KA01D,Engineering draft; verify ordered part and layout before fabrication,https://www.murata.com/en-global/products/productdetail?part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
C15,22u 25V X5R,power_asic,Back,5.579999,12.1,180.0,CoreSupport:Capacitor_SMD__C_1206_3216Metric,MSAST31LBB5226MTNA01,12 V design: 22 uF 25 V X5R 1206 correction. Manufacturer typical bias curve gives 6.62332 uF at 12.6 V; 0.8 tolerance and 0.85 temperature screening factors give 4.5038576 uF before aging. Local placement checked; routing integration pending in this separate revision. Typical curves are not guaranteed production minima.,https://ds.yuden.co.jp/TYCOMPAS/or/detail?pn=MSAST31LBB5226M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
C16,100n 100V X7R,power_asic,Back,8.729999,11.95,-90.0,CoreSupport:Capacitor_SMD__C_0603_1608Metric,GRM188R72A104KA35D,"12V candidate: manufacturer confirms 100nF +/-10%, 100V X7R, 0603, -55 to +125C and D packing suffix. Input bypass only; this voltage rating does not protect the 17V-rated converter input from cable transients.",https://www.murata.com/products/productdetail?partno=GRM188R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
C17,22u 16V X5R,power_asic,Back,2.079999,4.9,-90.0,CoreSupport:Capacitor_SMD__C_0805_2012Metric,EMK212BBJ226MG-T,"Engineering draft; verify ordered part and layout before fabrication Independent review: X5R, rated -55 to +85 C; manufacturer renamed alias MSASE21GBB5226MTNA01; effective capacitance and sourcing not qualified.",https://ds-origin.yuden.co.jp/TYCOMPAS/eu/detail?pn=MSASE21G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
C18,10n 50V X7R,power_asic,Back,8.579999,8.875,-90.0,CoreSupport:Capacitor_SMD__C_0603_1608Metric,GRM188R71H103KA01D,Engineering draft; verify ordered part and layout before fabrication,https://www.murata.com/en-global/products/productdetail?part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
C20,330u 2.5V POSCAP ESR9m@300kHz,decoupling_core,Back,11.9,32.15,0.0,CoreSupport:Panasonic_POSCAP_B2_Recommended,ETPE330M9GB,Compact bulk candidate;105C category max;ESR9m@300kHz20C;AMD ESL/PDN equivalence and load-step/ripple/thermal validation pending,https://industrial.panasonic.com/cdbs/www-data/pdf/AAA8000/A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
C21,100u 6.3V X5R,decoupling_bram,Back,24.85,7.8,-90.0,CoreSupport:Capacitor_SMD__C_1210_3225Metric,GRM32ER60J107ME20L,Engineering draft; verify ordered part and layout before fabrication Lifecycle review: manufacturer family listed NRND; confirm availability or qualify an alternate before release.,https://docs.amd.com/api/khub/documents/6L8DUUei7ZCE78qwQafC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
